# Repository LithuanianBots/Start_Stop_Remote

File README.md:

# Start_Stop_Remote

Start_Stop_Remote is a compact infrared remote designed for use with the MINI SUMO kit mainboard. It provides a small, robust controller for starting and stopping matches and is built with readily-available components to make assembly and sourcing easy.

Key features
- Remote uses IR SMD LEDs for a low-profile, reliable IR transmitter.
- Remote has additional IR LED footprints for standard 5 mm LEDs if you prefer through-hole components.
- PCB size: 80 mm x 40 mm — compact and easy to fit in a small enclosure.
- All free ATmega328 pins are routed to accessible solder pads so you can expand or repurpose the board.
- Most parts come from the LCSC basic parts library to simplify procurement.

Files and docs
- Full schematic and 3d files are available in the Docs folder:
  - Docs/Start_Stop_Remote.pdf
  - Docs/Start_Stop_Remote.step

Gallery (Top and Bottom views)
| TOP view | BOT view |
|---|---|
|  |  |

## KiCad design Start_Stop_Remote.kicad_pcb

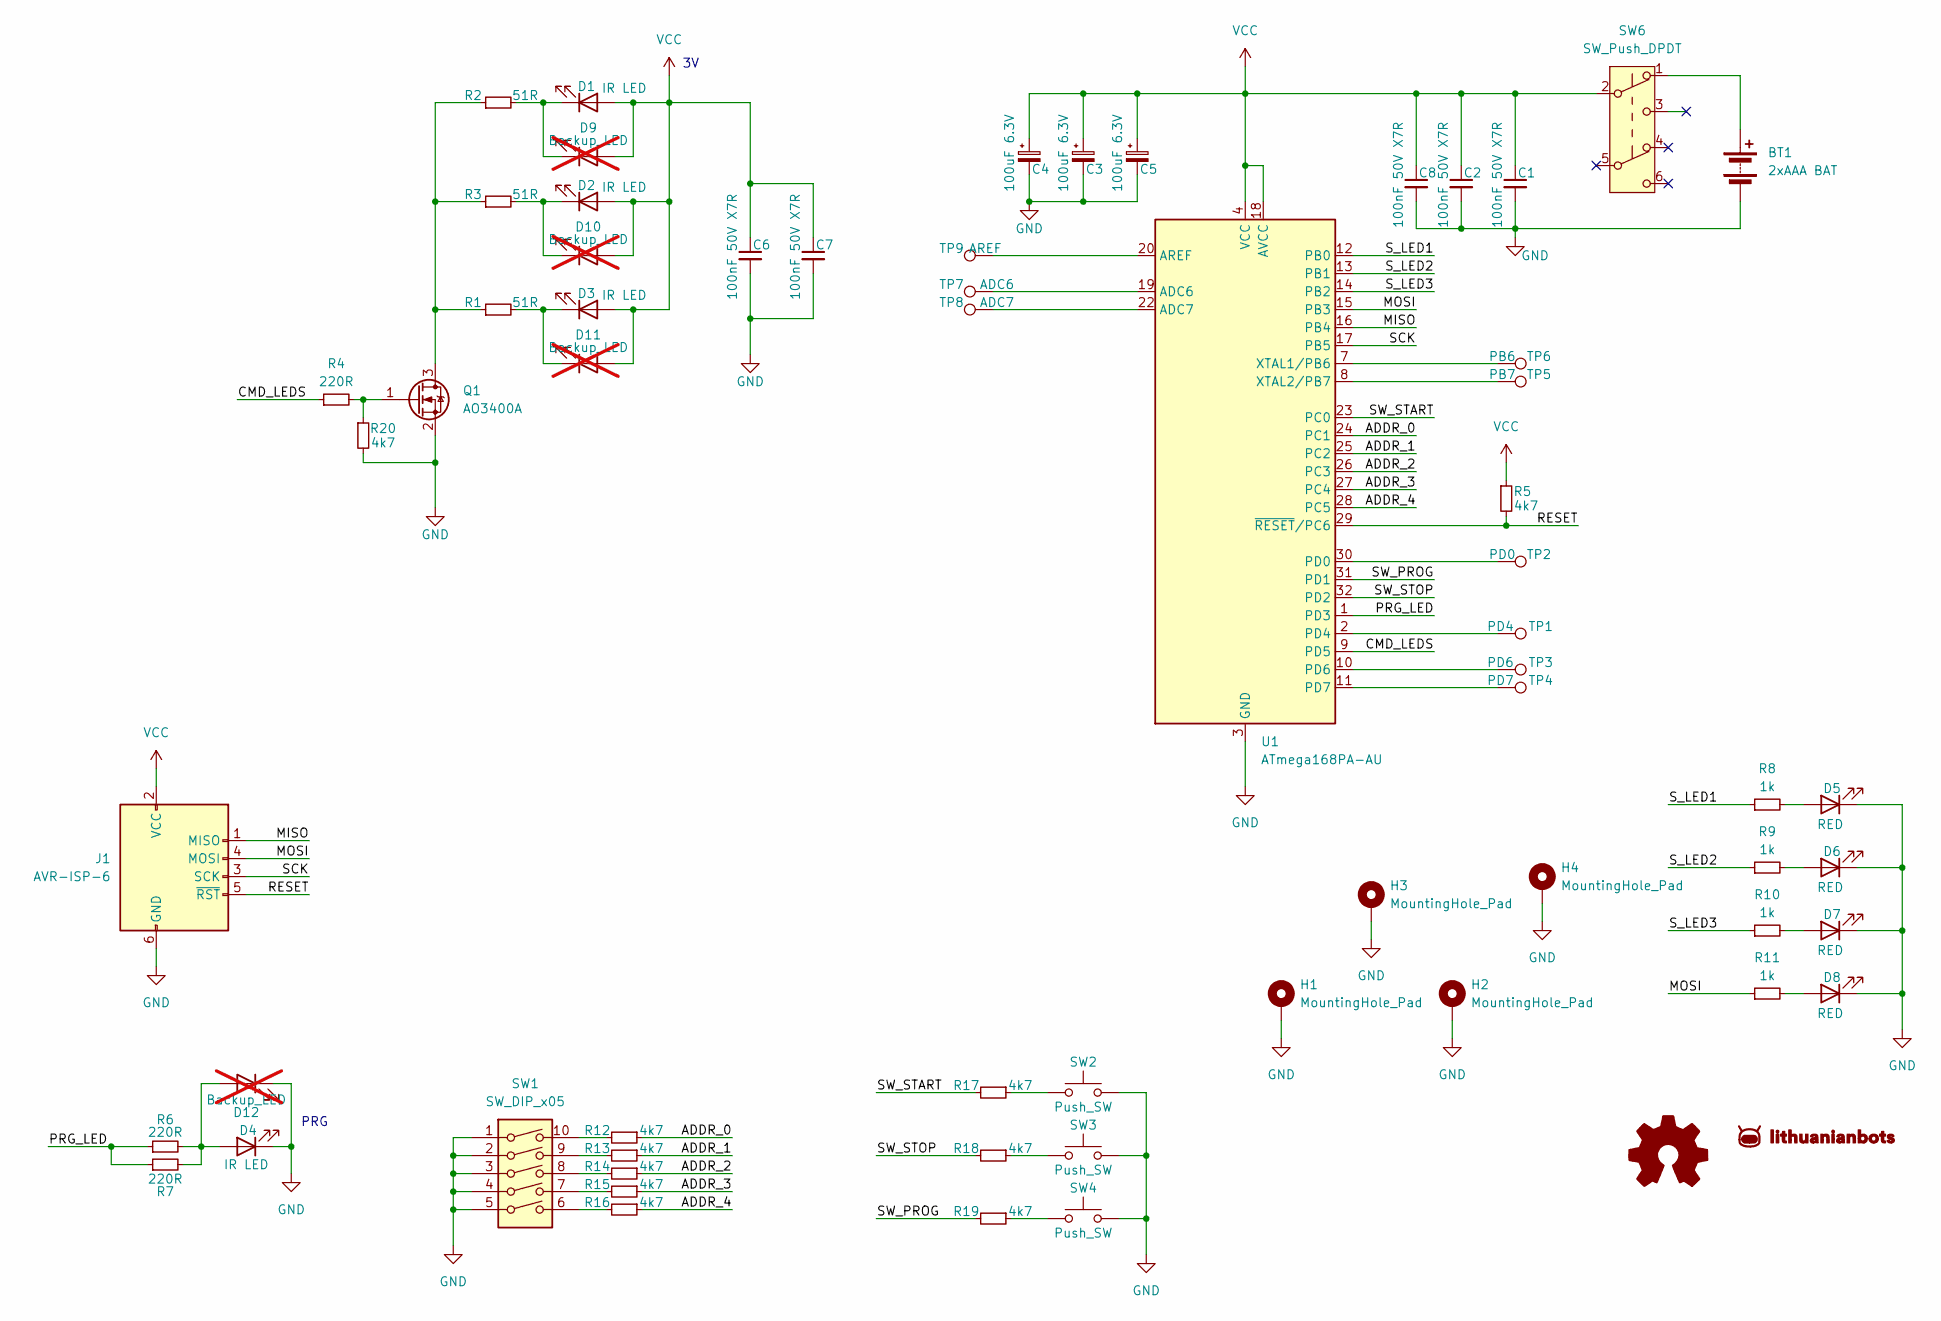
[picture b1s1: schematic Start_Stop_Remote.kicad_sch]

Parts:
BT1: 2xAAA BAT; BatteryHolder_-AAA-A1AJ020; LCSC C5290191
C1, C2, C6, C7, C8: 100nF 50V X7R; C_0603_1608Metric; LCSC C14663
C3, C4, C5: 100uF 6.3V; CP_EIA-3528-21_Kemet-B; LCSC C16133
D1, D2, D3, D4: IR LED; LED_LiteOn_LTST-S326; LCSC C5349963
D5, D6, D7, D8: RED; LED_0603_1608Metric; LCSC C2286
D9, D10, D11, D12: Backup_LED; LED_D5.0mm_Horizontal_O6.35mm_Z3.0mm; not fitted
H1, H2, H3, H4: MountingHole_Pad; MountingHole_3.2mm_M3_Pad_Via
J1: AVR-ISP-6; PinHeader_2x03_P2.54mm_Vertical; LCSC C65114
Q1: AO3400A; SOT-23; LCSC C20917
R1, R2, R3: 51R; R_0805_2012Metric; LCSC C17738
R4, R6, R7: 220R; R_0402_1005Metric; LCSC C25091
R5, R12, R13, R14, R15, R16, R17, R18, R19, R20: 4k7; R_0402_1005Metric; LCSC C25900
R8, R9, R10, R11: 1k; R_0402_1005Metric; LCSC C11702
SW1: SW_DIP_x05; SW_DIP_SPSTx05_Slide_9.78x14.88mm_W8.61mm_P2.54mm; LCSC C54951
SW2, SW3, SW4: Push_SW; SW_Push_1P1T_XKB_TS-1187A; LCSC C318884
SW6: SW_Push_DPDT; SW_CK_JS202011AQN_DPDT_Angled; LCSC C7507433
TP1: PD4; TestPoint_Pad_D1.0mm
TP2: PD0; TestPoint_Pad_D1.0mm
TP3: PD6; TestPoint_Pad_D1.0mm
TP4: PD7; TestPoint_Pad_D1.0mm
TP5: PB7; TestPoint_Pad_D1.0mm
TP6: PB6; TestPoint_Pad_D1.0mm
TP7: ADC6; TestPoint_Pad_D1.0mm
TP8: ADC7; TestPoint_Pad_D1.0mm
TP9: AREF; TestPoint_Pad_D1.0mm
U1: ATmega168PA-AU; LQFP-32_7x7mm_P0.8mm; LCSC C8728

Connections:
/ADDR_0: R12.1, U1.24 (PC1)
/ADDR_1: R13.1, U1.25 (PC2)
/ADDR_2: R14.1, U1.26 (PC3)
/ADDR_3: R15.1, U1.27 (PC4)
/ADDR_4: R16.1, U1.28 (PC5)
/CMD_LEDS: R4.1, U1.9 (PD5)
/MISO: J1.1 (MISO), U1.16 (PB4)
/MOSI: J1.4 (MOSI), R11.1, U1.15 (PB3)
/PRG_LED: R6.1, R7.1, U1.1 (PD3)
/RESET: J1.5 (~RST), R5.2, U1.29 (~RESET/PC6)
/SCK: J1.3 (SCK), U1.17 (PB5)
/SW_PROG: R19.2, U1.31 (PD1)
/SW_START: R17.2, U1.23 (PC0)
/SW_STOP: R18.2, U1.32 (PD2)
/S_LED1: R8.1, U1.12 (PB0)
/S_LED2: R9.1, U1.13 (PB1)
/S_LED3: R10.1, U1.14 (PB2)
GND: BT1.2 (-), C1.2, C2.2, C3.2, C4.2, C5.2, C6.2, C7.2, C8.2, D4.1 (K), D5.1 (K), D6.1 (K), D7.1 (K), D8.1 (K), D12.1 (K), H1.1, H2.1, H3.1, H4.1, J1.6 (GND), Q1.2 (S), R20.2, SW1.1, SW1.2, SW1.3, SW1.4, SW1.5, SW2.2, SW3.2, SW4.2, U1.3 (GND), U1.5 (GND), U1.21 (GND)
unnamed: BT1.1 (+), SW6.1 (A)
unnamed: D1.1 (K), D9.1 (K), R2.2
unnamed: D5.2 (A), R8.2
unnamed: D6.2 (A), R9.2
unnamed: D7.2 (A), R10.2
unnamed: D8.2 (A), R11.2
unnamed: D2.1 (K), D10.1 (K), R3.2
unnamed: D3.1 (K), D11.1 (K), R1.2
unnamed: D4.2 (A), D12.2 (A), R6.2, R7.2
unnamed: Q1.3 (D), R1.1, R2.1, R3.1
unnamed: Q1.1 (G), R4.2, R20.1
unnamed: R12.2, SW1.10
unnamed: R13.2, SW1.9
unnamed: R14.2, SW1.8
unnamed: R15.2, SW1.7
unnamed: R16.2, SW1.6
unnamed: R17.1, SW2.1
unnamed: R18.1, SW3.1
unnamed: R19.1, SW4.1
unnamed: TP7.1, U1.19 (ADC6)
unnamed: TP8.1, U1.22 (ADC7)
unnamed: TP9.1, U1.20 (AREF)
unnamed: TP2.1, U1.30 (PD0)
unnamed: TP1.1, U1.2 (PD4)
unnamed: TP3.1, U1.10 (PD6)
unnamed: TP4.1, U1.11 (PD7)
unnamed: TP6.1, U1.7 (XTAL1/PB6)
unnamed: TP5.1, U1.8 (XTAL2/PB7)
VCC: C1.1, C2.1, C3.1, C4.1, C5.1, C6.1, C7.1, C8.1, D1.2 (A), D2.2 (A), D3.2 (A), D9.2 (A), D10.2 (A), D11.2 (A), J1.2 (VCC), R5.1, SW6.2 (B), U1.4 (VCC), U1.6 (VCC), U1.18 (AVCC)

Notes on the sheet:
PRG

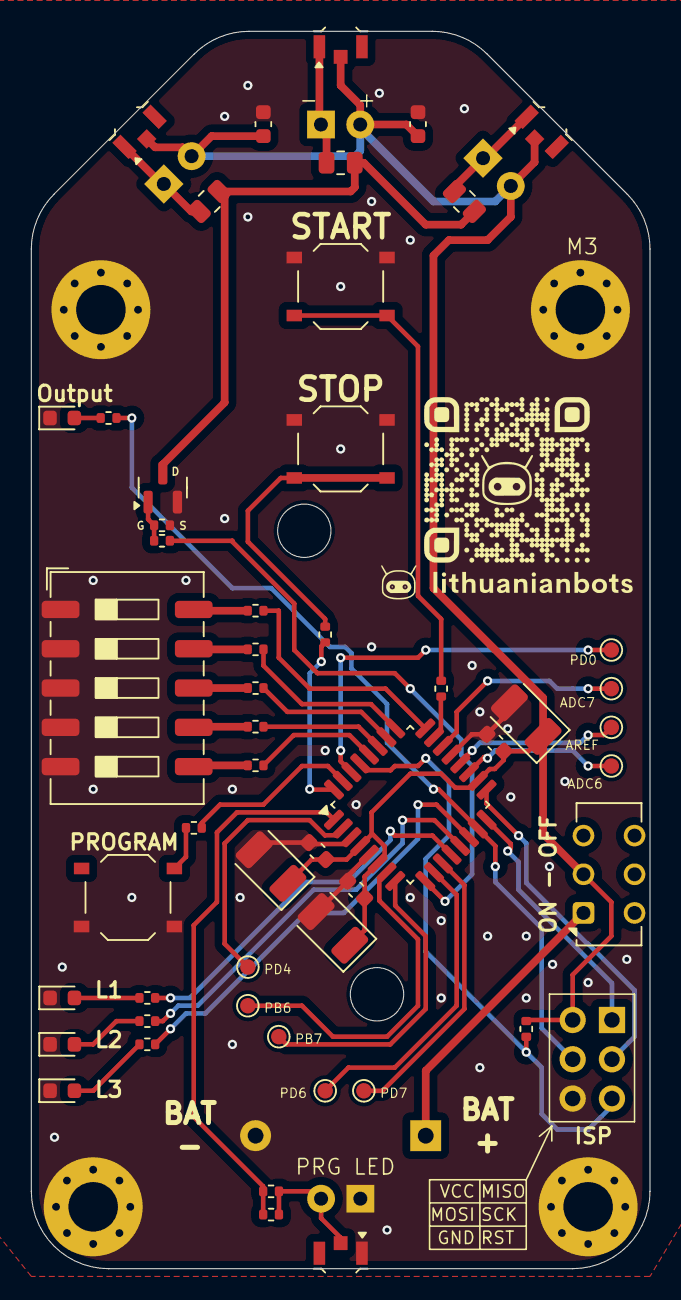
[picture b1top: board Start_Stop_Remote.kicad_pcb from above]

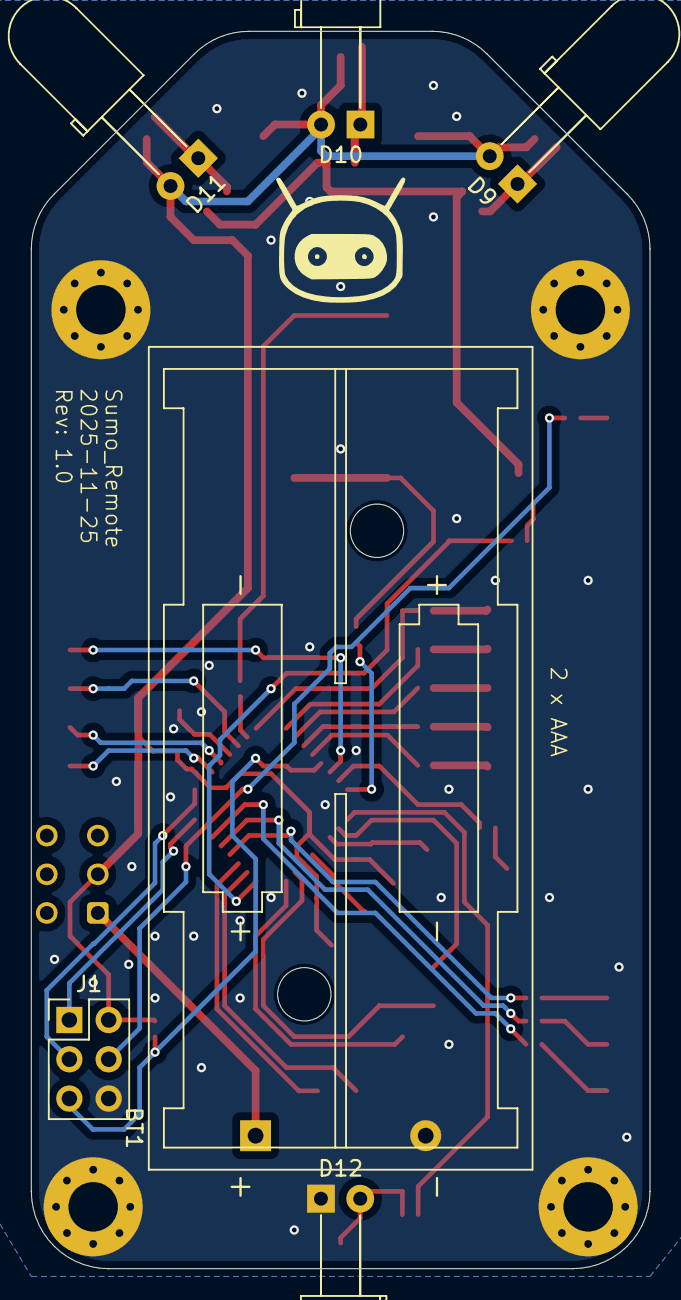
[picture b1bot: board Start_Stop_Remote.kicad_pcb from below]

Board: 2 copper layers, 40.0 x 80.0 mm, 62 parts (6 on the bottom side), 47 nets.

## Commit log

2025-11-25 Update gitignore
    Do not need to upload backups
2025-11-25 Added extra files
    Couple of pictures
    And schematic
2025-11-26 DRC fixes
    One trace routing fix near program button.
2025-11-26 Enhance README with product details and gallery
    Added detailed description and features of the Start_Stop_Remote.
2025-12-02 QR Code Update
    Old QR code was linked to an external website, that has paid service. New one - just links to https://lithuanianbots.com
    Library footprint updated as well.
